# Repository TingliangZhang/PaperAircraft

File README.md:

# PaperAircraft
https://en.wikipedia.org/wiki/Paper_plane

## V3版本

全新版本

电磁舵机+8mm空心杯+1S小锂电+电磁舵机接收机（集成5A电调）

2.4G带两路电磁舵驱动 5通道微型接收机 Futaba S-FHSS

https://item.taobao.com/item.htm?id=544533760584

遥控器兼容 S-FHSS即可

https://futabausa.com/product/14sg/

## 纸飞机

https://www.poweruptoys.com/

https://www.indiegogo.com/projects/powerup-4-0-smartphone-controlled-paper-airplane--2#/

https://item.taobao.com/item.htm?id=598983848365

https://detail.1688.com/offer/623588992739.html

看了这么多产品，最后还是要自己写飞控。通信用蓝牙或者Wifi，NanoBLESense可能又要用起来了。

https://item.taobao.com/item.htm?id=580652831242

小巧的7.8g高压锂电还是要用的

1.7g微型舵机

https://item.taobao.com/item.htm?id=610628423127

参考F3P和F1D

F3P

https://ultralight.tech/

https://www.bilibili.com/video/BV1Yk4y1971W

F1D

https://www.bilibili.com/video/BV1Q5411s7f6

可以考虑用共轴反桨，但是重量有点大，如果能开发微型共轴反桨，可以搞简单的直升机雪花。

## 一些想法

激光切割卡纸

BLE广播 mesh

## V1方案

元件选型

主控板：[Arduino Nano 33 BLE Sense](https://store.arduino.cc/usa/nano-33-ble-sense-with-headers)

3.3V能否接3.8V+存疑，考虑换DCDC芯片，但是[MPM3610](https://www.monolithicpower.cn/cn/mpm3610.html)的封装是节省空间的 QFN-20 (3mmx5mmx1.6mm)封装，很难找到相应的芯片以及更换。此路不通

外接一块3.8v-3.3v DCDC转换模块，找了一圈淘宝，找到DM13B-3.3，可以升降压。

[Arduino Nano 33 BLE](https://store.arduino.cc/usa/nano-33-ble)更便宜

新解决方案！电调上面的UBEC，UBEC输出:5.2V 2A（正负0.1V），原本给接收机用的，可以用来驱动Arduino！

电池：[Happymodel 3.8V 300mAh 30C 1-2S Lipo Battery PH2.0 Plug for Mobula6/7](http://www.happymodel.cn/index.php/2018/09/22/happymodel-3-8v-300mah-30c-1-2s-lipo-battery-ph2-0-plug-for-mobula7/)

https://item.taobao.com/item.htm?id=580652831242

Capacity:300mAh

Voltage:3.8v

Continuous Discharge Rate: 30C

Instantaneous discharge rate: 60C

Size: 57mmx12mmx7mm

Weight: 6.5g

Connector: PH2.0

充电器：[Happymodel Mobula7 FPV Racing Drone Spare Part 1S06 6 Way Lipo/LIHV Battery Charger](http://www.happymodel.cn/index.php/2018/08/31/happymodel-ur65-fpv-racing-drone-spare-part-1s06-6-way-lipolihv-battery-charger/)

https://item.taobao.com/item.htm?id=566199133982

4.20v cell charging cutoff (+- 0.5% margin of error) for 1S Lipo Battery

4.35v cell charging cutoff (+- 0.5% margin of error) for 1S 3.8V LIHV Battery

电机：暂时使用劣质的1.72块钱一个的[高速航模电机马达双环强磁716空心杯电机3.7V暴力50000转包邮](https://item.taobao.com/item.htm?id=535704086171)

规格:7x16x0.8mm 额定电压：3.7V 启动电压：0.15V 额定电流：800mA 额定转速：34000

舵机：[AFRC-D1302微型1.7g舵机MINI精致1.9g航模室内飞机直升机数字舵机 ](https://item.taobao.com/item.htm?spm=a1z09.2.0.0.2afc2e8doX2vub&id=607309316067)

尺寸:13.5 x 6.2 x 20.1 mm

重量:1.7g(不含线)

工作电压:3.7~5.0V

扭力:

3.7V：2.08 oz-in (0.15 kg-cm)

4.2V：2.36 oz-in (0.17 kg-cm)
速度:

3.7V：0.06 sec/60°

4.2V：0.04 sec/60°

出线: JST1.25mm L=110mm （棕-，红+，橙S）

直线电机：[AFRC-D1015直线舵机1.5克微型轻量迷你1.5g数字舵机](https://item.taobao.com/item.htm?spm=a1z09.2.0.0.2afc2e8doX2vub&id=611726187447)

尺寸:21.4 x 15.2 x 6.0 mm

重量:1.5g(不含线)

出线: JST1.25mm L=100 mm （红+，黑-，白S）；JST1.0mm,JR,Futaba L=100 mm （棕-，红+，橙S）

工作电压:3.7~6.0V

工厂默认行程为7mm/900~2100us

电机驱动：[1S超小微型单向有刷电调航模飞机固定翼空心杯电机专用驱动控制器](https://item.taobao.com/item.htm?id=548195280709)

最多能接4个空心杯电机;N20,N30,N50,131,180电机可以接2只.。

输入电池电压:2.2V-5.2V（超过5.5V烧电调）.

最大输出电:流20A.

UBEC输出:5.2V 2A.（正负0.1V）

## V2做PCB方案

自己画：STM32 蓝牙 IMU

or ESP32WROOM + IMU

STM32选型：STM32G031K8T6 STM32G031J6M6

PCB板上外设：

1. 蓝牙透传
2. IMU（目前可选）
3. 3.8v-3.3v降压稳压芯片
4. 空心杯电机驱动芯片
5. 电池电机舵机接口

具体选型

### DCDC芯片

TI电源解决方案[选型](https://www.ti.com/design-resources/design-tools-simulation.html)网站

[WEBENCH Power Designer](http://webench.ti.com/power-designer/switching-regulator)

[TLV62569DBVR](https://item.szlcsc.com/153167.html) 2A

[TLV62568DBVR](https://item.szlcsc.com/174600.html) 1A

这个很好用，能生成原理图和BOM。

甚至仿真

https://webench.ti.com/appinfo/webench/scripts/SDP.cgi?ID=C1D9EF81C082E009

TLV62568ADRLR及其周边电路BOM

[DC-DC芯片/TPS54331DR](https://item.szlcsc.com/10397.html)

[4.7uF(475) ±10% 10V](https://item.szlcsc.com/2057.html)

[10uF(106) ±20% 6.3V](https://item.szlcsc.com/2043.html)

[453KΩ ±1%](https://item.szlcsc.com/26561.html)

[100KΩ ±5%](https://item.szlcsc.com/16137.html)

[2.2uH ±20% 47mΩ 2.6A](https://item.szlcsc.com/503279.html)

[10uF(106) ±10% 10V](https://item.szlcsc.com/20411.html)无货更换为[10uF(106) ±20% 6.3V](https://item.szlcsc.com/2043.html)

### STM32

[STM32G031J6 ](https://www.st.com/en/microcontrollers-microprocessors/stm32g031j6.html)

Internal 16 MHz RC with PLL option 这玩意内部时钟16M感觉不用加外部时钟了，除非用得到48MHz

BOOT0用10k电阻拉低接地，boot from User Flash memory

加一个RST按钮，按下拉低RST

加入一个电源指示LED，以及一个接到PB9的LED

烧写用4pin杜邦线母头，接0/3.3V/TX/RX，使用ST-Link烧写程序

STM32G031J6及其周边电路BOM：

[STM32G031K8T6](https://item.szlcsc.com/428991.html)

[轻触开关 一型3x6x2.5有白ZD b拉伸白色按键 卷装](https://item.szlcsc.com/300030.html)

[1KΩ(1001) ±1%](https://item.szlcsc.com/116573.html)

[10KΩ(1002) ±1%](https://item.szlcsc.com/116572.html)

[100nF(104) ±10% 50V](https://item.szlcsc.com/1943.html)

[22Ω ±1%](https://item.szlcsc.com/24078.html)

[翠绿LED](https://item.szlcsc.com/207066.html)

可选晶振：[SMD3225 40.000MHZ 12PF 10PPM](https://item.szlcsc.com/420977.html)

### 电机驱动

[DRV8837CDSGR](https://item.szlcsc.com/213827.html)

### IMU

Arduino上面用的[LSM9DS1TR](https://www.digikey.cn/product-detail/zh/stmicroelectronics/LSM9DS1TR/497-14946-2-ND/4988083)在Digikey上面单个47.89块钱一个，太贵了

[MPU-6050](https://item.szlcsc.com/24852.html)嘉立创商城里也是10块钱左右

好贵，暂时不加了

### 蓝牙

都好贵，考虑ESP32了

[ESP32-WROOM-32](https://item.szlcsc.com/84060.html)

深圳大夏龙雀科技的蓝牙模块便宜点，十元以内

http://www.szdx-smart.com/

暂时选型[BT04-E低成本小体积无线串口透传蓝牙模组SPP3.0+BLE4.2蓝牙模块 ](https://item.taobao.com/item.htm?id=616730393533&_u=22q6uuheaa6e)

邮票孔版本。

Datasheet上面型号是，其实应该是Realtek RTL8762

本来想用[BT24高性价比串口高速透传BLE5.1微安级功耗蓝牙模块迷你无线模块](https://item.taobao.com/item.htm?id=621716432187&_u=22q6uuhea153)中的 DX-BT24-M[邮票孔贴片款] 但是不能更改参数，波特率或名字，就不太行。

封装用SOIC Footprint Wizard画

### 接口

电池接口选择PH2.0公头：[B2B-PH-K-S(LF)(SN)](https://item.szlcsc.com/142630.html)

电机接口 PH2.0公头：另一端需要母头压线端子 [PH2.0-T锡 编带](https://item.szlcsc.com/9392.html) 和胶壳 [胶壳 2.0mm 2Pin位](https://item.szlcsc.com/442393.html)

舵机接口 用[1.25T-1-3A](https://item.szlcsc.com/11366.html) 封装选用的Connector_Hirose:Hirose_DF13-03P-1.25DSA_1x03_P1.25mm_Vertical

烧写用4x2.54mm排针接在板上排母上[2.54x8.5排母 1x3P S/T](https://item.szlcsc.com/333717.html)

Futaba母头用3x2.54mm排针连接 [2.54-1*3P正弯针](https://item.szlcsc.com/93349.html)

## 气动设计

## 控制

### 舵机AFRC-D1302

[AFRC-D1302 Micro 1.7g Large Torque Mini Digital Servo for RC Airplane Fixed Wing Helicopter - JST 1.0 Plug](https://www.banggood.com/AFRC-D1302-Micro-1_7g-Large-Torque-Mini-Digital-Servo-for-RC-Airplane-Fixed-Wing-Helicopter-p-1618521.html?ID=6285197&cur_warehouse=CN)

这俩都是333Hz，所以3ms周期，0.9-2.1ms对应-55到55 degree角度。

裂开了，这玩意真的是3ms，不是20ms周期！

太邪教了，换一个正常点的舵机：[2.2克超微型数字舵机 PZ-15318](https://item.taobao.com/item.htm?spm=a1z09.2.0.0.334a2e8dFbH5WX&id=591162573182&_u=32q6uuhe6ed0)

PWM, 50HZ， 高电平时间在1~2ms

工作电压：2.5V-4.8V

注意不到5V，不能接到Arduino5V端口。

### 直线电机AFRC-D1015

[AFRC-D10115 1.5g Linear Servo Miniature Micro Lightweight with Digital Controller for AFRC-D1015 Indoor 3D Small RC Aircraft - JR Plug](https://www.banggood.com/AFRC-D10115-1_5g-Linear-Servo-Miniature-Micro-Lightweight-with-Digital-Controller-for-AFRC-D1015-Indoor-3D-Small-RC-Aircraft-p-1619274.html?ID=520802&cur_warehouse=CN)

### 电机和驱动

正常电调的控制信号范围是1000us到2000us，一个周期20ms。

买的这个是直流有刷电机电调

用[Servo](https://www.arduino.cc/reference/en/libraries/servo/)库

```c
servo.attach(pin, min, max);
myservo.write(angle); // set servo to 0 - 180
```

拔了USB之后电机就转了23333

更精确控制用

```c
myservo.writeMicroseconds(1500);  // set servo to mid-point
```

### 蓝牙

The communications chipset on the Nano 33 BLE can be both a BLE and Bluetooth client and host device. Something pretty unique in the world of microcontroller platforms. If you want to see how easy it is to create a Bluetooth central or a peripheral device, explore the examples at our [ArduinoBLE library](https://www.arduino.cc/en/Reference/ArduinoBLE).

classic参考

[Arduino Bluetooth Basic Tutorial](https://create.arduino.cc/projecthub/mayooghgirish/arduino-bluetooth-basic-tutorial-d8b737?ref=platform&ref_id=424_popular___&offset=1)

BLE参考

[Arduino BLE Example Explained Step by Step](https://rootsaid.com/arduino-ble-example/)

[Arduino BLE Accelerometer Tutorial for Beginners](https://rootsaid.com/arduino-ble-accelerometer-tutorial/)

注意：电脑中打开串口监视器才启动蓝牙设备Bluetooth device active, waiting for connections...

You can use a generic BLE central app, like LightBlue (iOS and Android) or nRF Connect (Android), to interact with the services and characteristics created in this sketch.

[Using Bluetooth 4.0 "classic" with Arduino Nano 33 BLE?](https://forum.arduino.cc/index.php?topic=649306.msg4378833#msg4378833)

绝望，没有 bluetooth classic ，BLE连不上Bluetooth Electronics，所以没办法搞GUI。

### IMU

[Arduino_LSM9DS1](https://github.com/arduino-libraries/Arduino_LSM9DS1)Allows you to read the accelerometer, magnetometer and gyroscope values from the LSM9DS1 IMU on your Arduino Nano 33 BLE Sense.

### ESP32

[ESP32 BLE Arduino](https://www.arduino.cc/reference/en/libraries/esp32-ble-arduino/)

### 蓝牙模块

模块未连接时为AT 模式，连接上后为透传模式

## 程序编写

Arduino端的程序就是读取UART，操控舵机和电机，手机端的Bluetooth Electronics可以定义UI推杆和摇杆，并且可以定义开始位和结束位。

Serial是USB，Serial1是D0 and D1即TX RX。

[Serial](https://www.arduino.cc/reference/en/language/functions/communication/serial/) Reference

一个Servo库的bug，我调了半天最后，更新了一下下Servo库，就好了。。。

AXY算出来多了528......原因未知。先减528再说。。。。。

## 涉及软件

Kicad

[Fritzing](https://fritzing.org/)

官网下载要8欧，直接Github[fritzing-app](https://github.com/fritzing/fritzing-app)中找到[CD-548](https://github.com/fritzing/fritzing-app/releases/tag/CD-548)发布0.9.5

http://fritzing.org/download/0.9.3b/windows-64bit/fritzing.0.9.3b.64.pc.zip

## 调试

螺旋桨or电风扇

竟然螺旋桨是反着吹的。我说怎么打死飞不起来。。。

20201104 22：30 第一次完整程序测试，电调灯时亮时灭，有短路。舵机只有一个转，另一个不转，可能是代码有问题或者舵机坏了。查了没发现代码问题，明天早上去换一下看看转不转。

波形信号都对。最终发现是电调的连接线掉了。。。以及舵机本身就是3ms的周期，现在写的是20ms，等新的舵机到。

新的舵机到了，很好用。

电机到75%才开始转，而且没看出来调速功能，以及转的不如直接接电池快。

破案了：75的时候电调才开始被驱动，76的时候信号灯才亮。

尝试发现信号范围竟然是1800-2300us。。。

20201106连不上BT04-E问题解决：先配对，之后用nRF Connect连接一次，关闭程序后，用Bluetooth Electronics连接，不行就重启

### Bluetooth Electronics APP内设置

## V2成果

## Seeeduino XIAO

[Seeeduino XIAO - Arduino Microcontroller - SAMD21 Cortex M0+](https://www.seeedstudio.com/Seeeduino-XIAO-Arduino-Microcontroller-SAMD21-Cortex-M0+-p-4426.html)

This is the [Wiki](http://wiki.seeedstudio.com/Seeeduino-XIAO/) of the Seeeduino XIAO

## PCB设计

## V3成本估计

控制成本到10元级别，选用STM32G031K8T6或ESP32-WROOM-32，DRV8837C，TLV62568DBV

| 品名                                                         | 目前购买价（RMB） | 量产价 |
| ------------------------------------------------------------ | ----------------- | ------ |
| [ICM-20600](https://invensense.tdk.com/products/motion-tracking/6-axis/icm-20600/) | 1.38              |        |
| STM32G031K8T6                                                | 4.81              |        |
| DRV8837C                                                     | 0.5561            |        |
| TLV62568DBV                                                  | 1.0181            |        |
| 其他连接件3D打印                                             | 2                 |        |
| PCB                                                          | 1                 |        |

## V2时间线

| 倒计时N天 | 肝的活                                                       |
| --------- | ------------------------------------------------------------ |
| 7         | 确定做纸飞机，选型V1核心板，设计大致的架构                   |
| 6         | 开始担心重量问题，画了V2的PCB，jlc买元件，赶着下打样订单，蓝牙HC-05和IMU-6050太贵，暂时没找到便宜的，没画完。 |
| 5         | 大批购买元件，顺丰空运要第二天到，利用手头的元件测试舵机。叠各种构型纸飞机载重试飞，确定上反角+翼尖小翼气动构型。 |
| 4         | 2.2g舵机和BT-04E到货，调蓝牙通信，以及供电解决方案，通过电调解决。 |
| 3         | 测试整体系统成功，代码整体测试通过。                         |
| 2         | 焊了一天的线，BT04模块贴片引脚太小了，焊了俩小时，小体积的   |
| 1         | 上午整机组装试飞，拍视频。                                   |

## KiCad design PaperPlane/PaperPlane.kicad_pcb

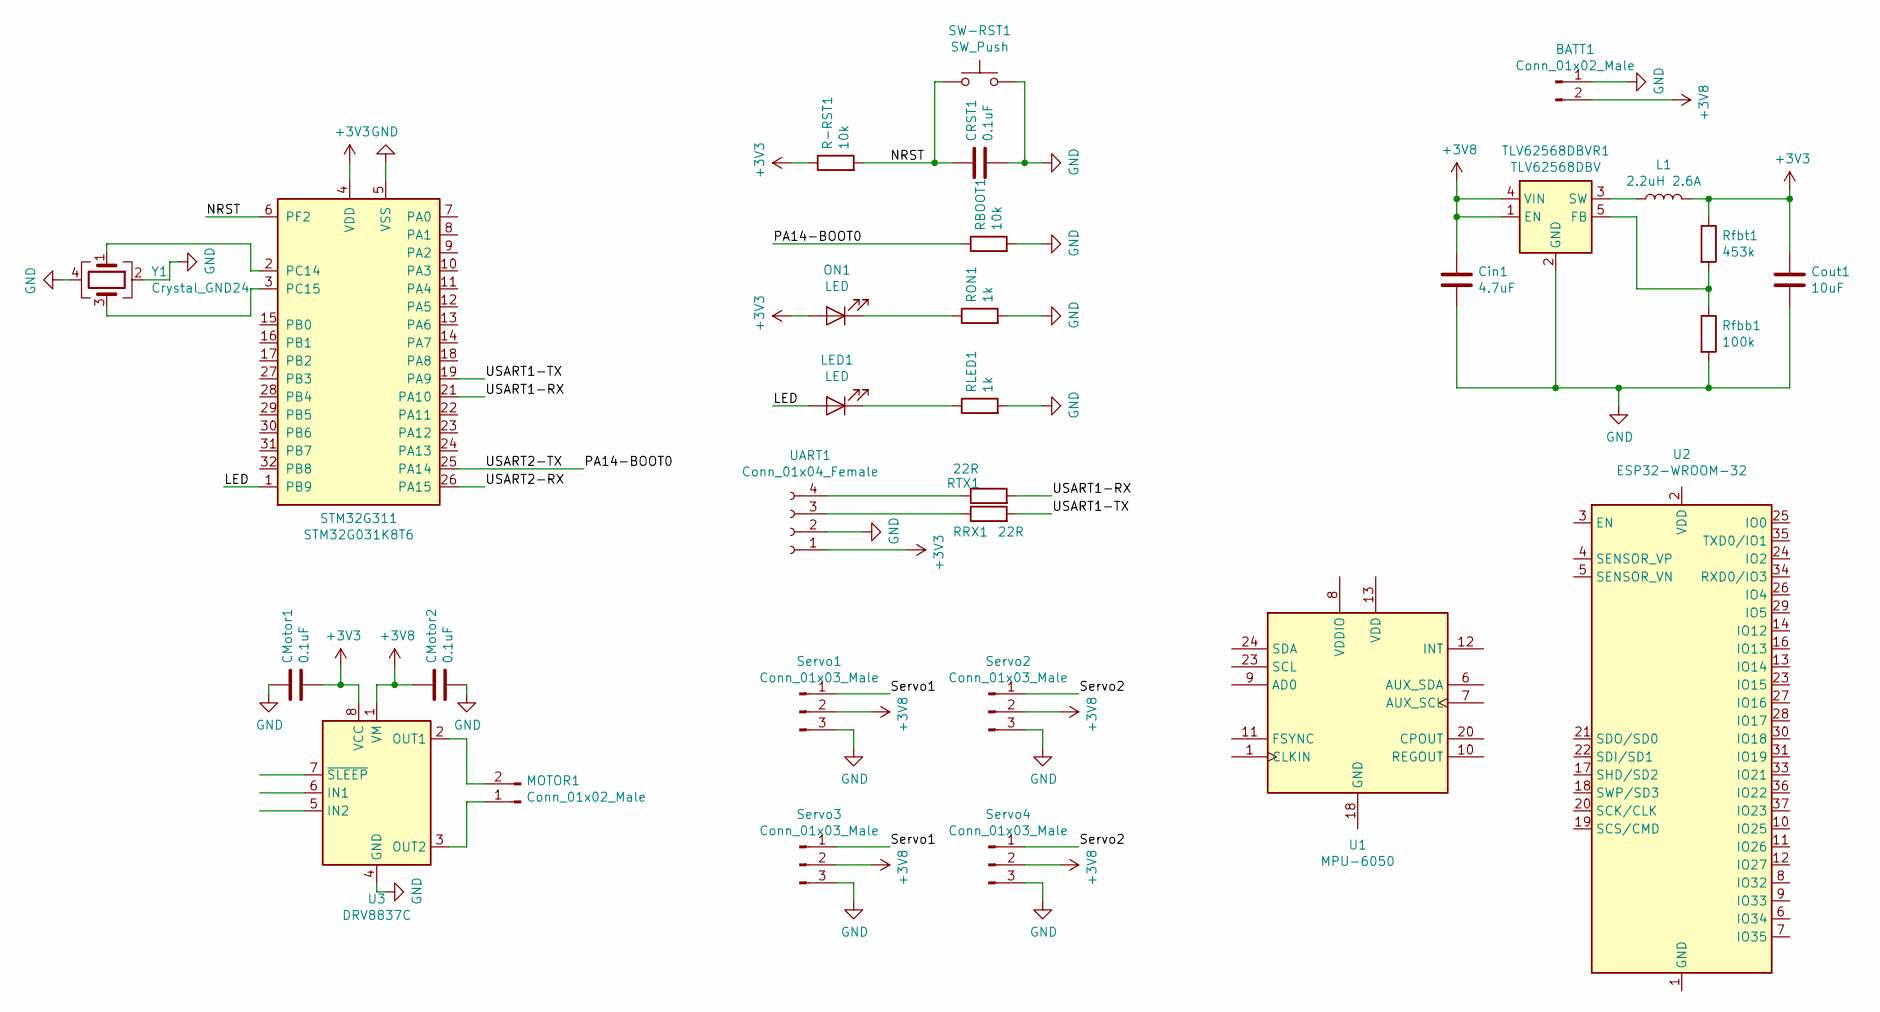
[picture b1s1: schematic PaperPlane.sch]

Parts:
BATT1: Conn_01x02_Male; JST_PH_B2B-PH-K_1x02_P2.00mm_Vertical
CMotor1, CMotor2: 0.1uF; C_0603_1608Metric
CRST1: 0.1uF; C_0603_1608Metric
Cin1: 4.7uF; C_0603_1608Metric
Cout1: 10uF; C_0603_1608Metric
L1: 2.2uH 2.6A; L_Taiyo-Yuden_NR-50xx_HandSoldering
LED1: LED; LED_0603_1608Metric
MOTOR1: Conn_01x02_Male; JST_PH_B2B-PH-K_1x02_P2.00mm_Vertical
ON1: LED; LED_0603_1608Metric
R-RST1: 10k; R_0603_1608Metric
RBOOT1: 10k; R_0603_1608Metric
RLED1: 1k; R_0603_1608Metric
RON1: 1k; R_0603_1608Metric
RRX1: 22R; R_0603_1608Metric
RTX1: 22R; R_0603_1608Metric
Rfbb1: 100k; R_0603_1608Metric
Rfbt1: 453k; R_0603_1608Metric
STM32G311: STM32G031K8T6; LQFP-32_7x7mm_P0.8mm
SW-RST1: SW_Push; TACTILE_SWITCH_SMD_6.0X3.5MM
Servo1, Servo2: Conn_01x03_Male; Hirose_DF13-03P-1.25DSA_1x03_P1.25mm_Vertical
Servo3, Servo4: Conn_01x03_Male; PinHeader_1x03_P2.54mm_Horizontal
TLV62568DBVR1: TLV62568DBV; SOT-23-5
U1: MPU-6050; InvenSense_QFN-24_4x4mm_P0.5mm
U2: ESP32-WROOM-32
U3: DRV8837C; WSON-8-1EP_2x2mm_P0.5mm_EP0.9x1.6mm
UART1: Conn_01x04_Female; PinSocket_1x04_P2.54mm_Vertical
Y1: Crystal_GND24; Crystal_SMD_3225-4Pin_3.2x2.5mm

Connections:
+3V3: CMotor1.2, Cout1.1, L1.2, ON1.2 (A), R-RST1.1, Rfbt1.1, STM32G311.4 (VDD), U3.8 (VCC), UART1.1
+3V8: BATT1.2, CMotor2.1, Cin1.1, Servo1.2, Servo2.2, Servo3.2, Servo4.2, TLV62568DBVR1.1 (EN), TLV62568DBVR1.4 (VIN), U3.1 (VM)
/LED: LED1.2 (A), STM32G311.1 (PB9)
/NRST: CRST1.1, R-RST1.2, STM32G311.6 (PF2), SW-RST1.1
/PA14-BOOT0: RBOOT1.1, STM32G311.25 (PA14)
/Servo1: Servo1.1, Servo3.1
/Servo2: Servo2.1, Servo4.1
/USART1-RX: RTX1.2, STM32G311.21 (PA10)
/USART1-TX: RRX1.2, STM32G311.19 (PA9)
GND: BATT1.1, CMotor1.1, CMotor2.2, CRST1.2, Cin1.2, Cout1.2, RBOOT1.2, RLED1.2, RON1.2, Rfbb1.2, STM32G311.5 (VSS), SW-RST1.2, Servo1.3, Servo2.3, Servo3.3, Servo4.3, TLV62568DBVR1.2 (GND), U3.4 (GND), U3.9 (GND), UART1.2, Y1.2, Y1.4
unnamed: L1.1, TLV62568DBVR1.3 (SW)
unnamed: LED1.1 (K), RLED1.1
unnamed: MOTOR1.1, U3.3 (OUT2)
unnamed: MOTOR1.2, U3.2 (OUT1)
unnamed: ON1.1 (K), RON1.1
unnamed: RRX1.1, UART1.3
unnamed: RTX1.1, UART1.4
unnamed: Rfbb1.1, Rfbt1.2, TLV62568DBVR1.5 (FB)
unnamed: STM32G311.2 (PC14), Y1.1
unnamed: STM32G311.3 (PC15), Y1.3
unnamed: U2.1 (GND), U2.15 (GND), U2.38 (GND), U2.39 (GND)

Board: 2 copper layers, 30 parts (0 on the bottom side), 21 nets, no tracks yet.

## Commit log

2020-10-31 PCB TLV62568DBVR
2020-10-31 PCB sch
2020-10-31 Add STM32G031K8T6
2020-10-31 HalfFinish
2020-11-01 ServoExplore
2020-11-02 BL-04E
2020-11-03 ADD swdio swclk
2020-11-03 Fritzing
2020-11-04 serial
2020-11-04 ERROR
2020-11-04 println
2020-11-04 count
2020-11-04 Finish send and recieve data
2020-11-04 Really Finish data process
2020-11-04 Hope it will work
2020-11-04 第一次完整程序测试
2020-11-05 Signal correct
2020-11-05 Debug Motor
2020-11-05 RESULT
2020-11-06 presentation
